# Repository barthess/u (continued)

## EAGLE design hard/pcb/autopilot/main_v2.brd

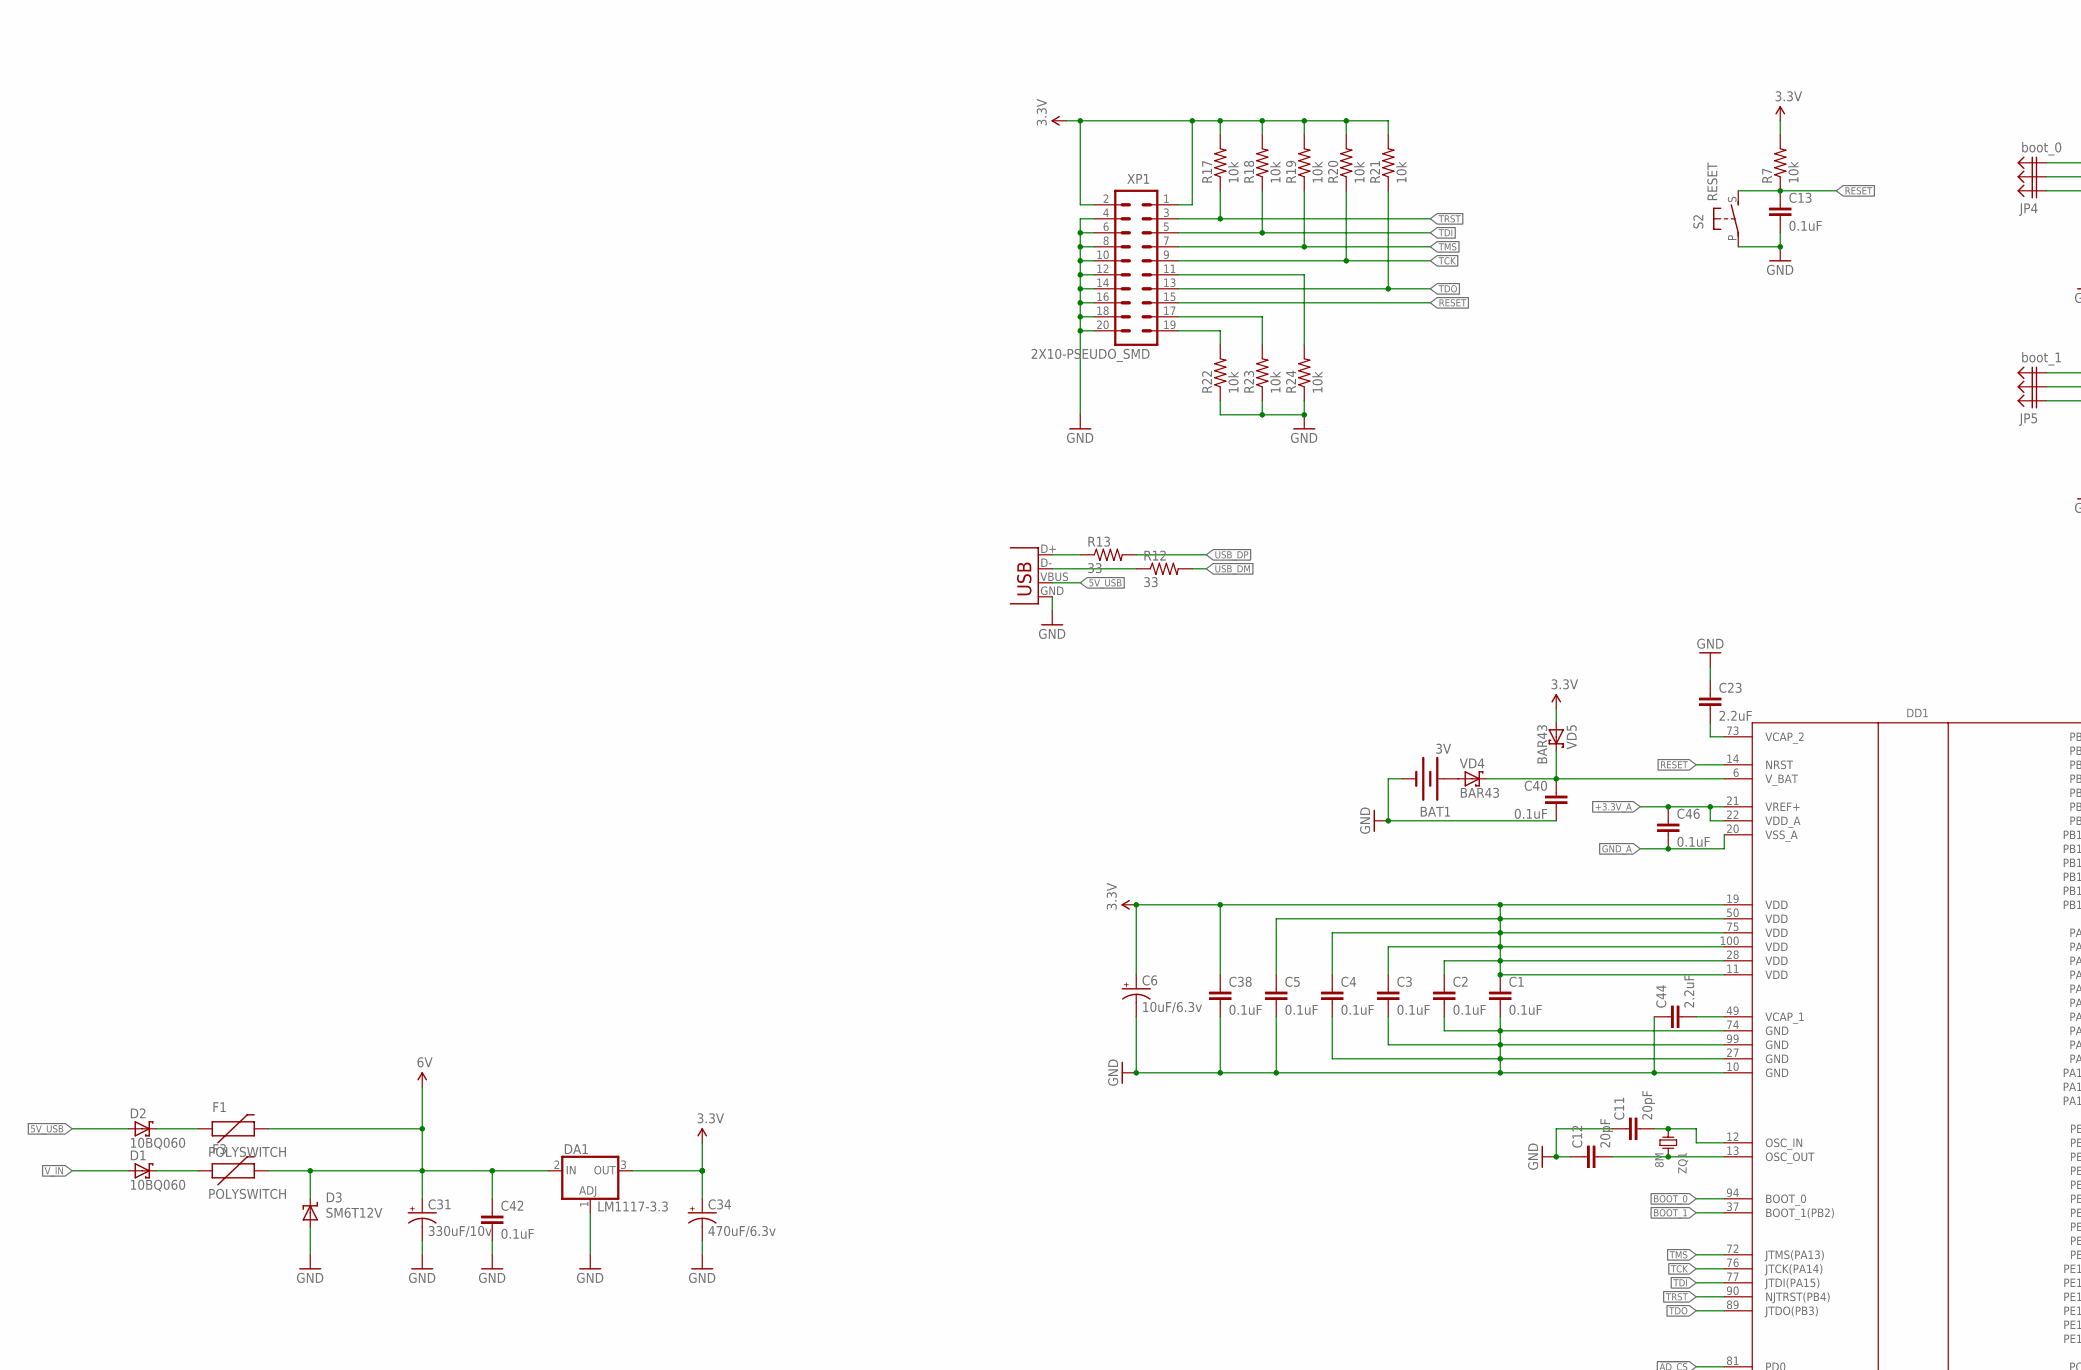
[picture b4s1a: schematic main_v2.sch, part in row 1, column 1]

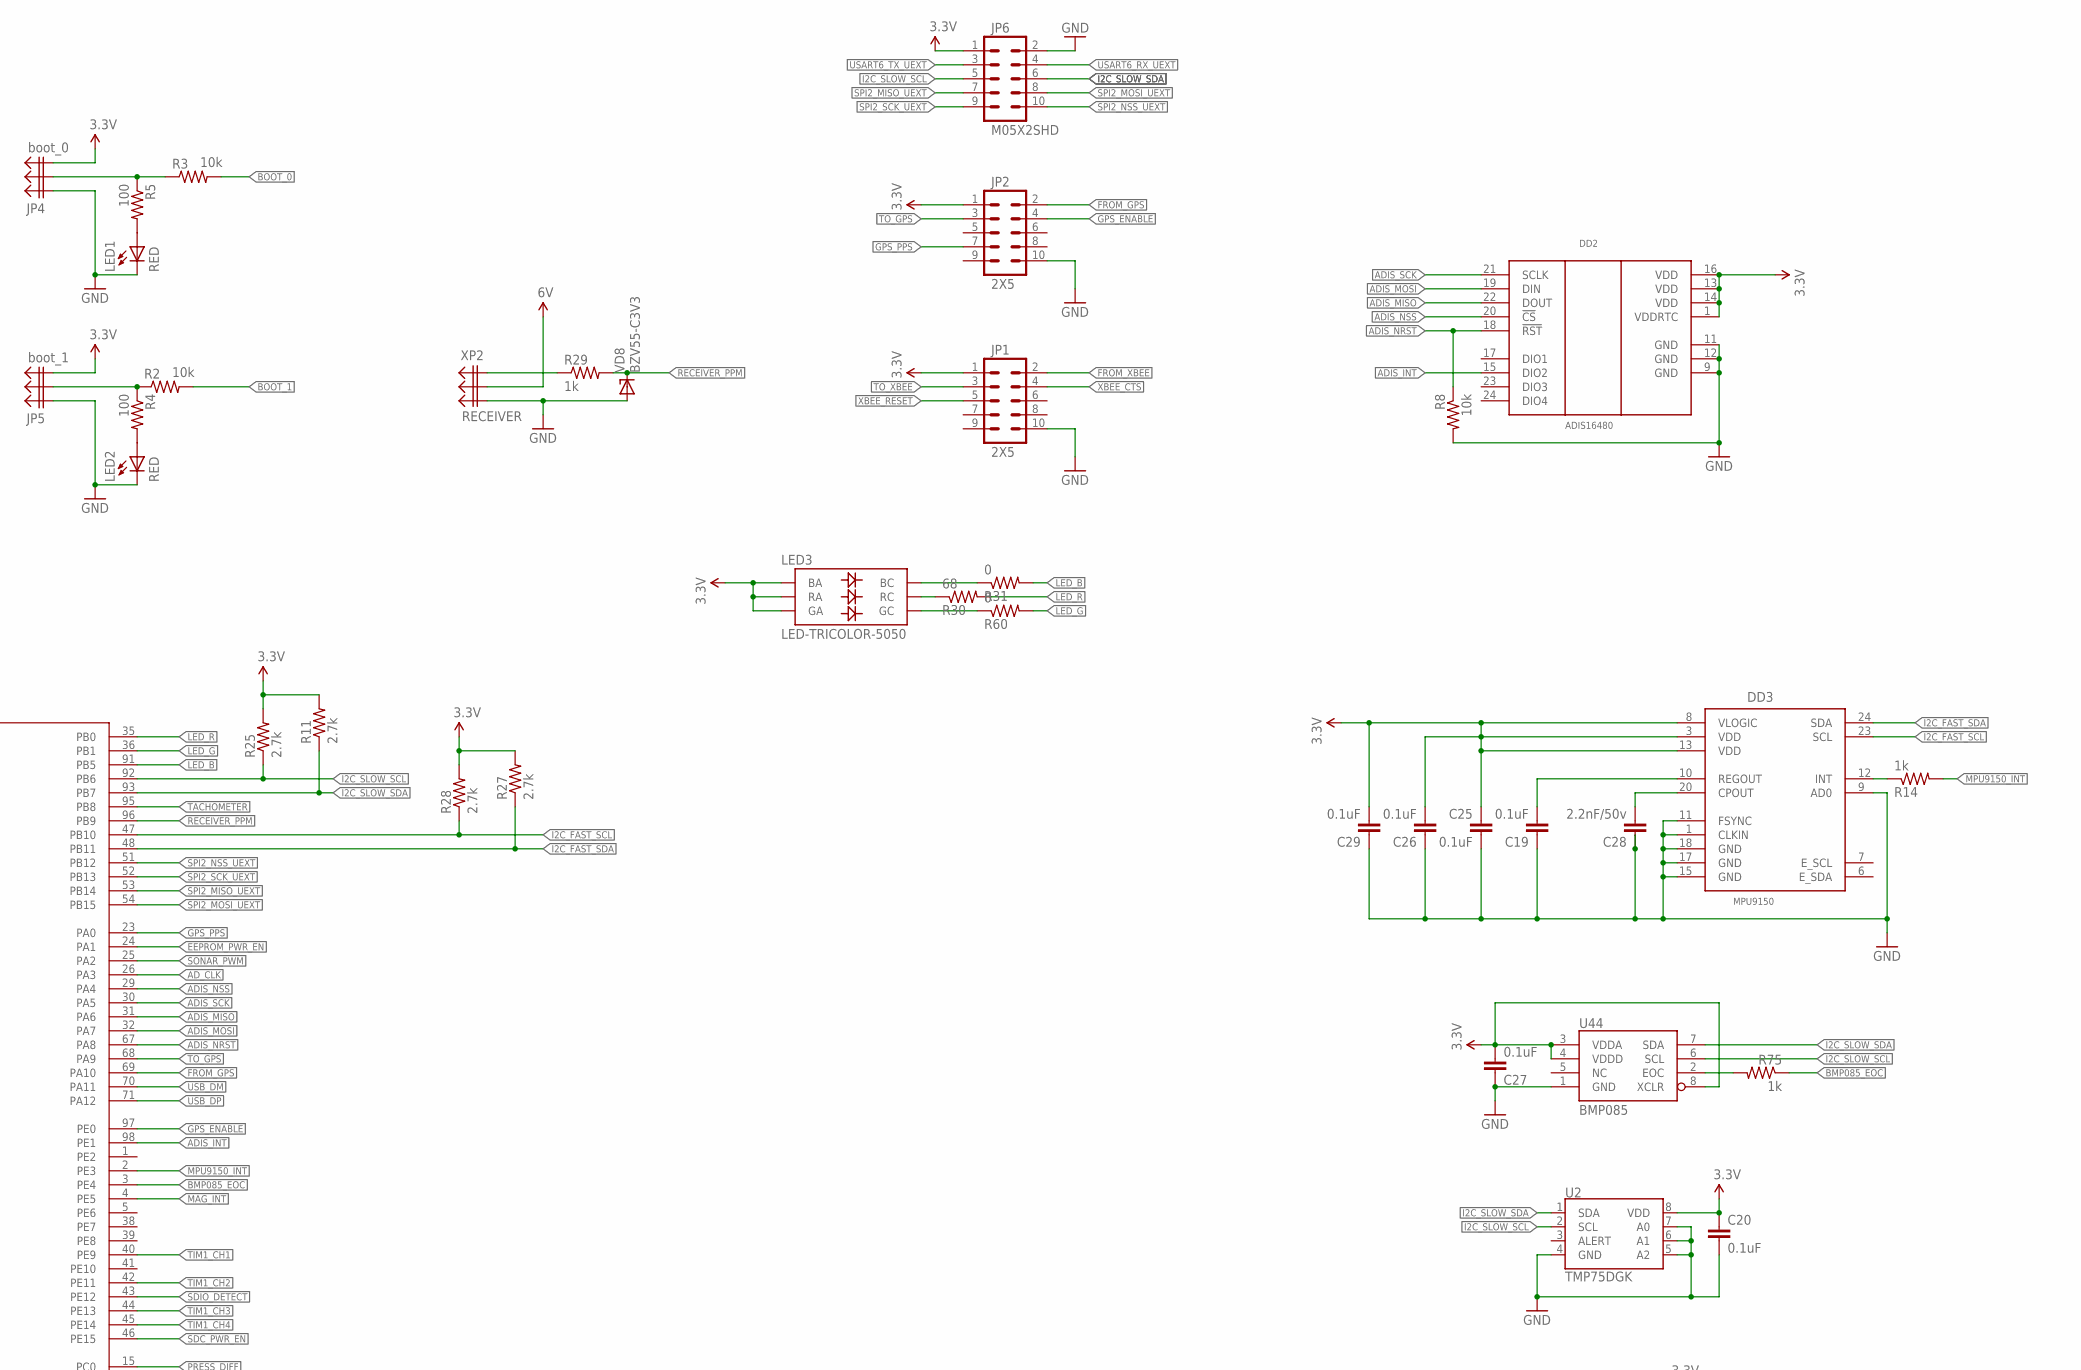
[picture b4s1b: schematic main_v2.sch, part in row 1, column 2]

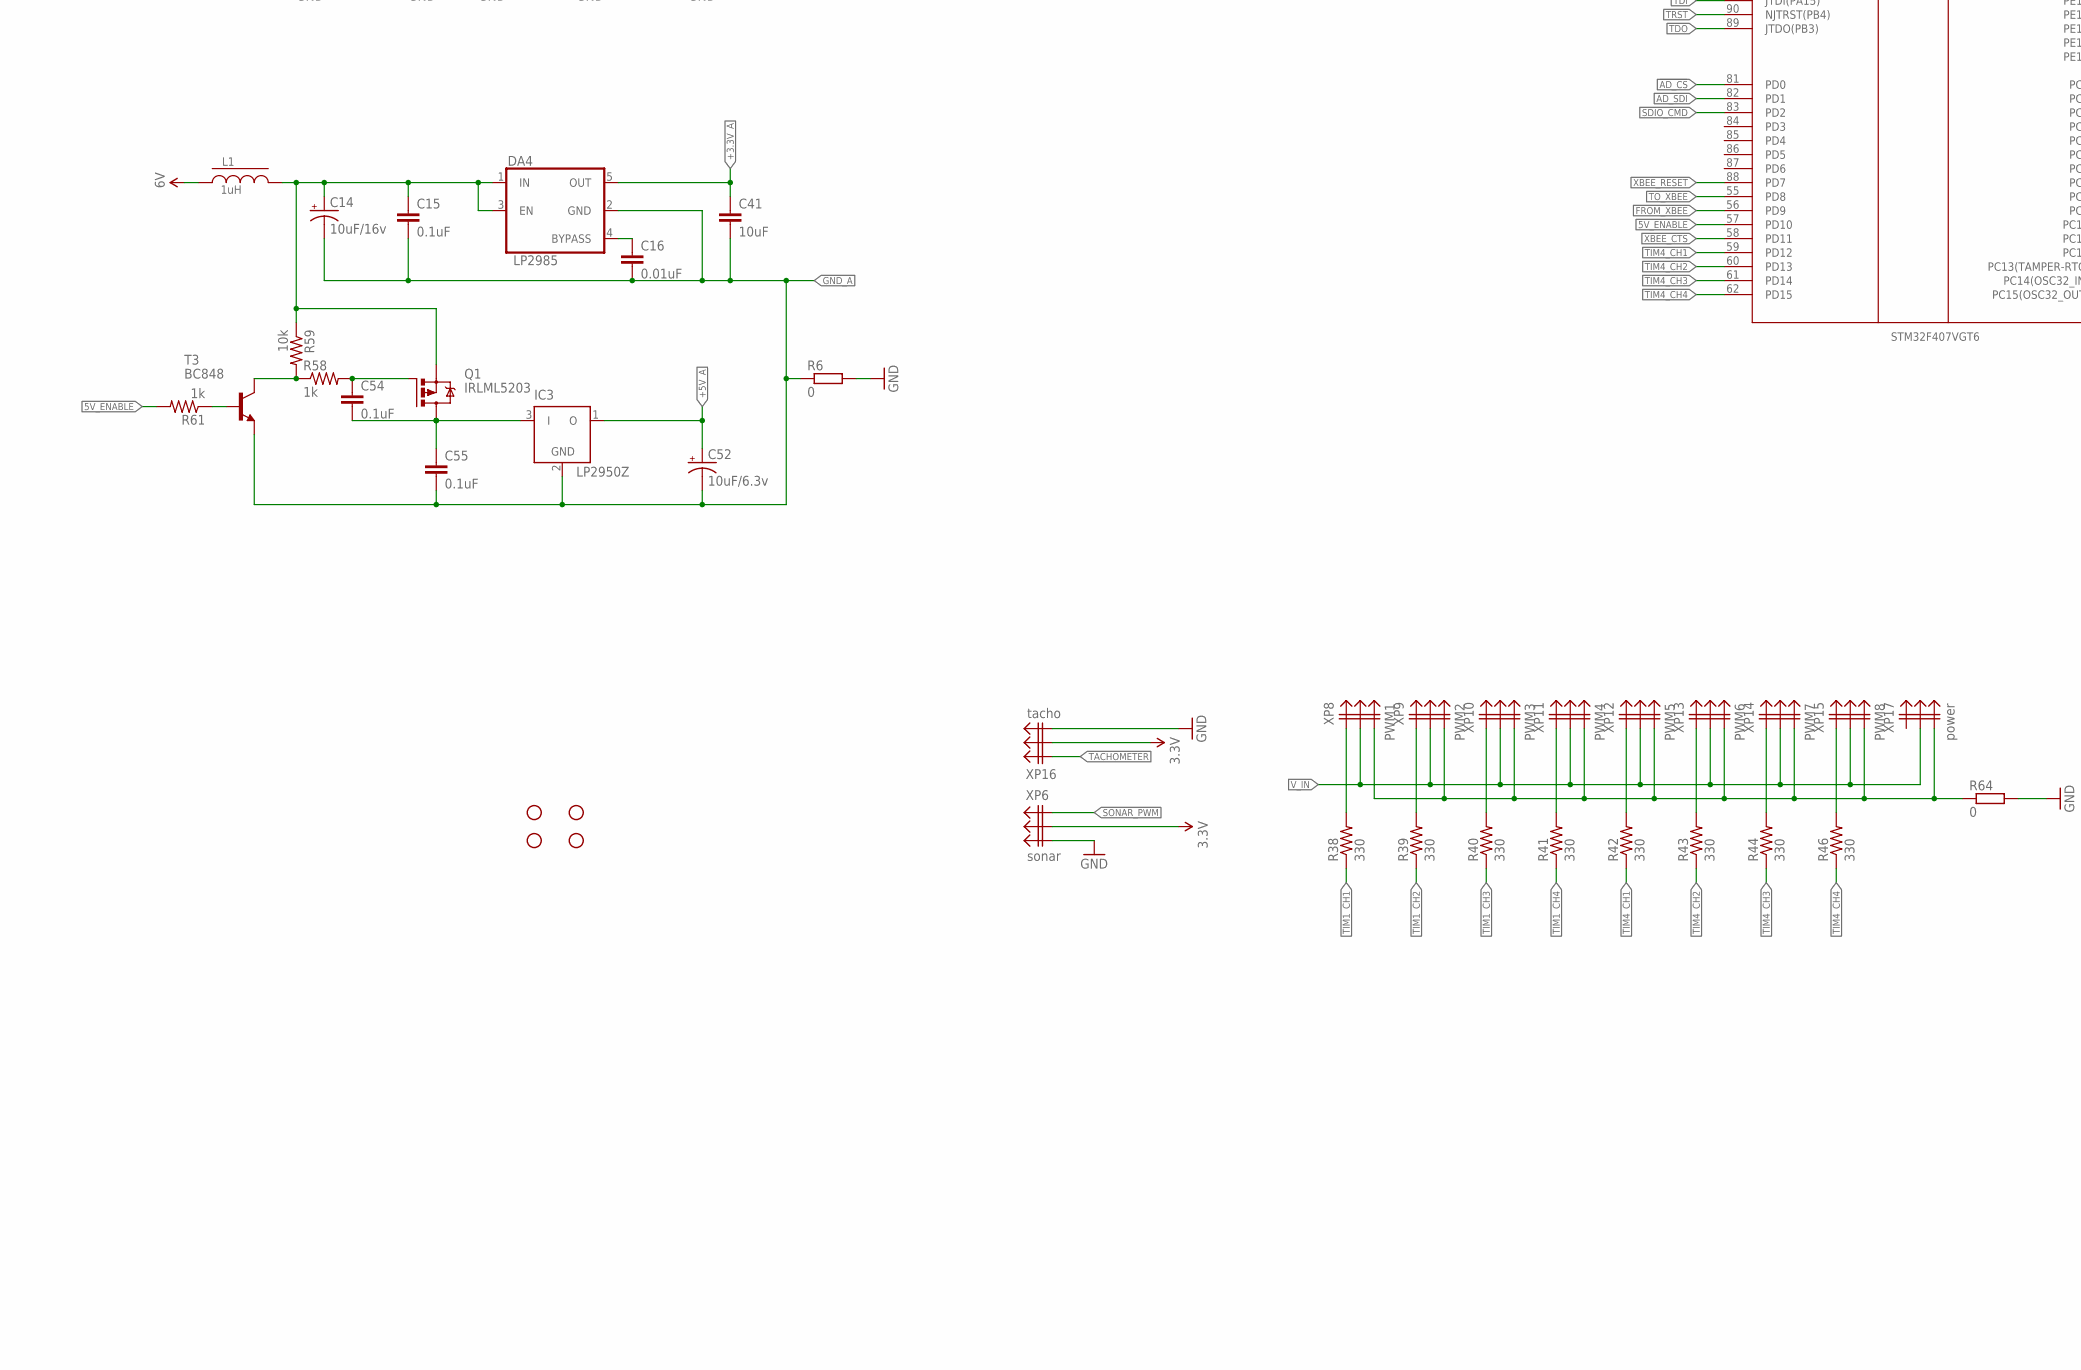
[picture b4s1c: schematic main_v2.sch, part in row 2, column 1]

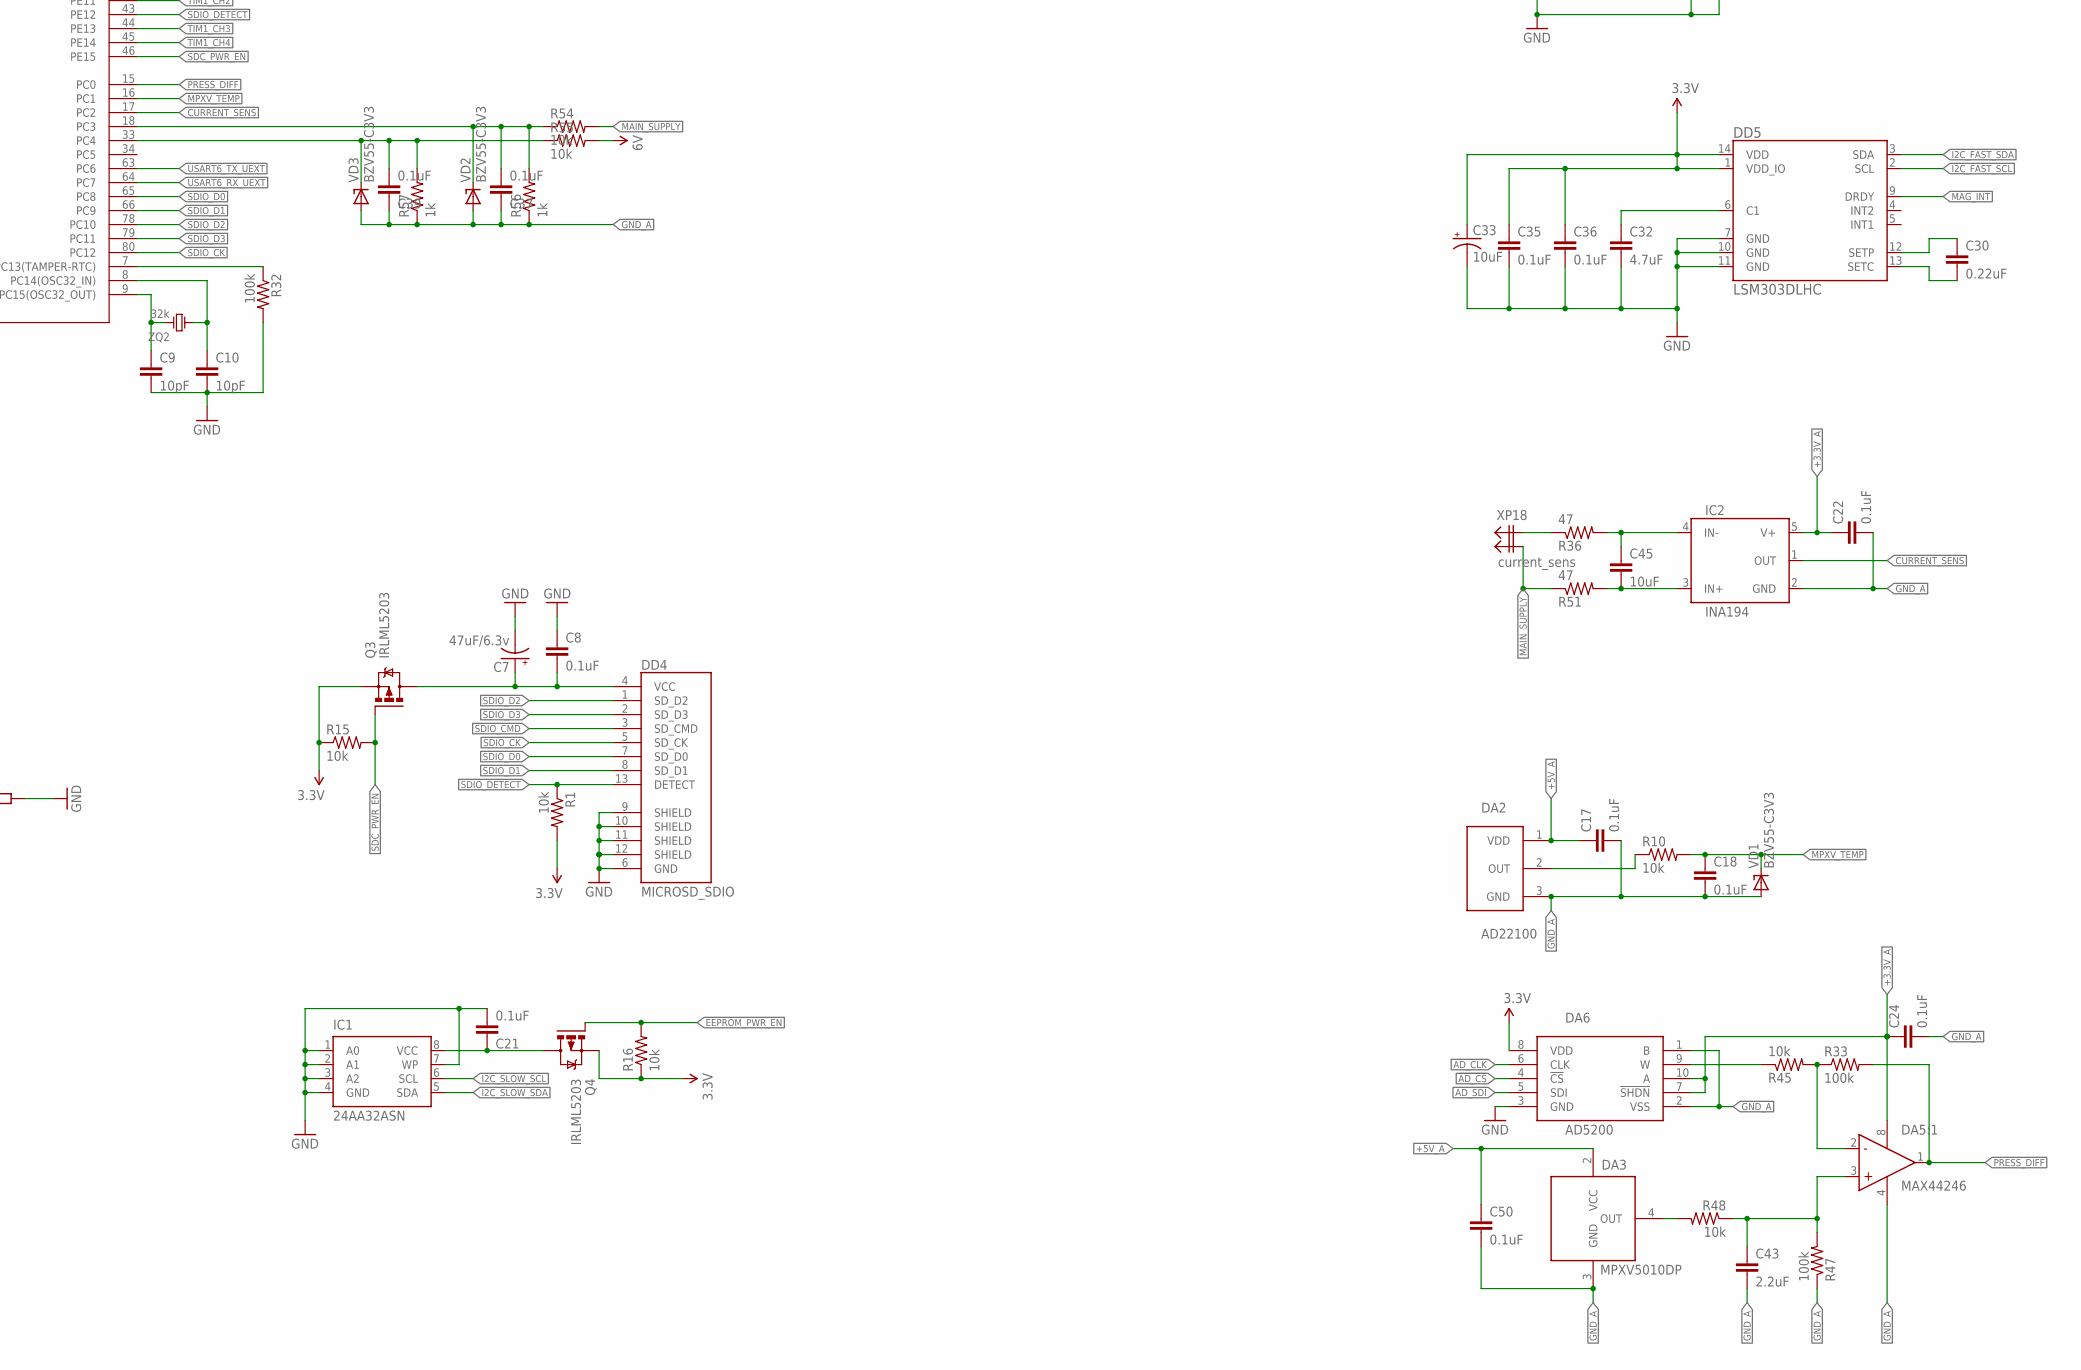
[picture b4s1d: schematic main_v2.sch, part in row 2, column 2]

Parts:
BAT1: 3V; BATTCOM_20MM_PTH
C1, C2, C3, C4, C5, C8, C13, C15, C17, C18, C19, C20, C21, C22, C24, C25, C26, C27, C29, C35, C36, C37, C38, C39, C40, C42, C46, C50, C54, C55: 0.1uF; 0805
C6, C52: 10uF/6.3v; EIA3216-KIT
C7: 47uF/6.3v; EIA3216-KIT
C9, C10: 10pF; 0805
C11, C12: 20pF; 0805
C14: 10uF/16v; EIA3216-KIT
C16: 0.01uF; 0805
C23, C43, C44: 2.2uF; 0805
C28: 2.2nF/50v; 0805
C30: 0.22uF; 0805
C31: 330uF/10v; EIA7343
C32: 4.7uF; 0805
C33: 10uF; EIA3216-KIT
C34: 470uF/6.3v; EIA7343
C41, C45: 10uF; 1206
D1, D2: 10BQ060; SMB
D3: SM6T12V; SMBJ
DA1: LM1117-3.3; TO252
DA2: AD22100; TO92
DA3: MPXV5010DP; 482
DA4: LP2985; SOT23-5
DA5: MAX44246; MSOP8
DA6: AD5200; MSOP10
DD1: STM32F407VGT6; TQFP100
DD2: ADIS16480
DD3: MPU9150; QFN-24-NP
DD4: MICROSD_SDIO; MICROSD
DD5: LSM303DLHC; LGA14
F1, F3: POLYSWITCH; 1812
IC1: 24AA32ASN; SO-08
IC2: INA194; SOT23-5
IC3: LP2950Z; TO92
JP1, JP2: 2X5; PLD_2X05_PSEUDOSMD
JP3, JP7, JP8, JP9: STAND-OFF
JP4: boot_0; PLD_1X03
JP5: boot_1; PLD_1X03
JP6: M05X2SHD; 2X5-SHROUDED
L1: 1uH; L0603
LED1, LED2: RED; LED-0805
LED3: LED-TRICOLOR-5050
Q1, Q3, Q4: IRLML5203; MICRO3
R1, R2, R3, R7, R8, R10, R15, R16, R17, R18, R19, R20, R21, R22, R23, R24, R45, R48, R54, R55, R59: 10k; 0805
R4, R5: 100; 0805
R6, R64: 0; 1206
R11, R25, R27, R28: 2.7k; 0805
R12, R13: 33; 0805
R14, R29, R56, R57, R58, R61, R75: 1k; 0805
R30: 68; 0805
R31, R60: 0; 0805
R32, R33, R47: 100k; 0805
R36, R51: 47; 0805
R38, R39, R40, R41, R42, R43, R44, R46: 330; 0805
S2: RESET; BUTTON_6X3.5
T3: BC848; SOT23
U2: TMP75DGK; MSOP8
U44: BMP085
VD1, VD2, VD3, VD8: BZV55-C3V3; SOD80C
VD4, VD5: BAR43; SOT23-3
X1: USB-SMD-NS; USB-MINIB-NOSTOP
XP1: 2X10-PSEUDO_SMD; PLD_2X10_PSEUDOSMD
XP2: RECEIVER; PLD_1X03
XP6: sonar; PLD_1X03
XP8: PWM1; PLD_1X03
XP9: PWM2; PLD_1X03
XP10: PWM3; PLD_1X03
XP11: PWM4; PLD_1X03
XP12: PWM5; PLD_1X03
XP13: PWM6; PLD_1X03
XP14: PWM7; PLD_1X03
XP15: PWM8; PLD_1X03
XP16: tacho; PLD_1X03
XP17: power; PLD_1X03
XP18: current_sens; PLD_1X02
ZQ1: 8M; CRYSTAL-SMD-5X3
ZQ2: 32k; CRYSTAL-32KHZ-SMD-3.2X1.5

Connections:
3.3V: C1.1, C2.1, C3.1, C4.1, C5.1, C6.A (+), C20.1, C25.1, C26.2, C27.2, C29.2, C33.A (+), C34.A (+), C35.1, C36.1, C38.1, DA1.3 (OUT), DA6.8 (VDD), DD1.11 (VDD), DD1.19 (VDD), DD1.28 (VDD), DD1.50 (VDD), DD1.75 (VDD), DD1.100 (VDD), DD2.1 (VDDRTC), DD2.13 (VDD), DD2.14 (VDD), DD2.16 (VDD), DD3.3 (VDD), DD3.8 (VLOGIC), DD3.13 (VDD), DD5.1 (VDD_IO), DD5.14 (VDD), JP1.1, JP2.1, JP4.3, JP5.3, JP6.1, LED3.1 (BA), LED3.2 (RA), LED3.3 (GA), Q3.2 (S), Q4.2 (S), R1.2, R7.2, R11.2, R15.1, R16.1, R17.2, R18.2, R19.2, R20.2, R21.2, R25.2, R27.2, R28.2, U2.8 (VDD), U44.3 (VDDA), U44.4 (VDDD), U44.8 (XCLR), VD5.1 (A), XP1.1, XP1.2, XP6.2, XP16.2
5V_ENABLE: DD1.57 (PD10), R61.2
5V_USB: D2.A, X1.VBUS
6V: C31.A (+), C42.1, D3.C, DA1.2 (IN), F1.2, F3.2, L1.1, R55.2, XP2.2
!AD_CS: DA6.4 (!CS), DD1.81 (PD0)
+3.3V_A: C22.1, C24.1, C41.1, C46.1, DA4.5 (OUT), DA5.8 (+V), DA6.7 (!SHDN), DA6.10 (A), DD1.21 (VREF+), DD1.22 (VDD_A), IC2.5 (V+)
+5V_A: C17.1, C50.1, C52.A (+), DA2.1 (VDD), DA3.2 (VCC), IC3.1 (O)
ADIS_INT: DD1.98 (PE1), DD2.15 (DIO2)
ADIS_MISO: DD1.31 (PA6), DD2.22 (DOUT)
ADIS_MOSI: DD1.32 (PA7), DD2.19 (DIN)
ADIS_NRST: DD1.67 (PA8), DD2.18 (!RST), R8.1
ADIS_NSS: DD1.29 (PA4), DD2.20 (!CS)
ADIS_SCK: DD1.30 (PA5), DD2.21 (SCLK)
AD_CLK: DA6.6 (CLK), DD1.26 (PA3)
AD_SDI: DA6.5 (SDI), DD1.82 (PD1)
BMP085_EOC: DD1.3 (PE4), R75.1
BOOT_0: DD1.94 (BOOT_0), R3.2
BOOT_1: DD1.37 (BOOT_1(PB2)), R2.2
CURRENT_SENS: DD1.17 (PC2), IC2.1 (OUT)
EEPROM_PWR_EN: DD1.24 (PA1), Q4.1 (G), R16.2
FROM_GPS: DD1.69 (PA10), JP2.2
FROM_XBEE: DD1.56 (PD9), JP1.2
GND: BAT1.2 (-), C1.2, C2.2, C3.2, C4.2, C5.2, C6.C (-), C7.C (-), C8.1, C9.2, C10.2, C11.1, C12.1, C13.2, C19.1, C20.2, C21.2, C23.1, C25.2, C26.1, C27.1, C28.1, C29.1, C31.C (-), C32.2, C33.C (-), C34.C (-), C35.2, C36.2, C38.2, C40.2, C42.2, C44.1, D3.A, DA1.1 (ADJ), DA6.3 (GND), DD1.10 (GND), DD1.27 (GND), DD1.74 (GND), DD1.99 (GND), DD2.9 (GND), DD2.11 (GND), DD2.12 (GND), DD3.1 (CLKIN), DD3.9 (AD0), DD3.11 (FSYNC), DD3.15 (GND), DD3.17 (GND), DD3.18 (GND), DD4.6 (GND), DD4.9 (SHIELD), DD4.10 (SHIELD), DD4.11 (SHIELD), DD4.12 (SHIELD), DD5.7 (GND), DD5.10 (GND), DD5.11 (GND), IC1.1 (A0), IC1.2 (A1), IC1.3 (A2), IC1.4 (GND), IC1.7 (WP), JP1.10, JP2.10, JP4.1, JP5.1, JP6.2, LED1.C, LED2.C, R6.2, R8.2, R22.1, R23.1, R24.1, R32.2, R64.2, S2.P, U2.4 (GND), U2.5 (A2), U2.6 (A1), U2.7 (A0), U44.1 (GND), VD8.A, X1.GND, XP1.4, XP1.6, XP1.8, XP1.10, XP1.12, XP1.14, XP1.16, XP1.18, XP1.20, XP2.3, XP6.3, XP16.3
GND_A: C14.C (-), C15.2, C16.2, C17.2, C18.2, C22.2, C24.2, C37.1, C39.1, C41.2, C43.2, C46.2, C50.2, C52.C (-), C55.2, DA2.3 (GND), DA3.3 (GND), DA4.2 (GND), DA5.4 (-V), DA6.1 (B), DA6.2 (VSS), DD1.20 (VSS_A), IC2.2 (GND), IC3.2 (GND), R6.1, R47.1, R56.1, R57.1, T3.2 (E), VD1.A, VD2.A, VD3.A
GPS_ENABLE: DD1.97 (PE0), JP2.4
GPS_PPS: DD1.23 (PA0), JP2.7
I2C_FAST_SCL: DD1.47 (PB10), DD3.23 (SCL), DD5.2 (SCL), R28.1
I2C_FAST_SDA: DD1.48 (PB11), DD3.24 (SDA), DD5.3 (SDA), R27.1
I2C_SLOW_SCL: DD1.92 (PB6), IC1.6 (SCL), JP6.5, R25.1, U2.2 (SCL), U44.6 (SCL)
I2C_SLOW_SDA: DD1.93 (PB7), IC1.5 (SDA), JP6.6, R11.1, U2.1 (SDA), U44.7 (SDA)
LED_B: DD1.91 (PB5), R31.2
LED_G: DD1.36 (PB1), R60.2
LED_R: DD1.35 (PB0), R30.2
MAG_INT: DD1.4 (PE5), DD5.9 (DRDY)
MAIN_SUPPLY: R51.1, R54.2, XP18.2
MPU9150_INT: DD1.2 (PE3), R14.2
MPXV_TEMP: C18.1, DD1.16 (PC1), R10.2, VD1.C
unnamed: C9.1, DD1.9 (PC15(OSC32_OUT)), ZQ2.2
unnamed: LED2.A, R4.2
unnamed: JP5.2, R2.1, R4.1
unnamed: LED1.A, R5.2
unnamed: JP4.2, R3.1, R5.1
unnamed: C10.1, DD1.8 (PC14(OSC32_IN)), ZQ2.1
unnamed: C12.2, DD1.13 (OSC_OUT), ZQ1.3
unnamed: LED3.6 (BC), R31.1
unnamed: C11.2, DD1.12 (OSC_IN), ZQ1.1
unnamed: R12.1, X1.D-
unnamed: DA6.9 (W), R45.1
unnamed: LED3.5 (RC), R30.1
unnamed: R13.1, X1.D+
unnamed: D1.C, F3.1
unnamed: C16.1, DA4.4 (BYPASS)
unnamed: DA2.2 (OUT), R10.1
unnamed: R22.2, XP1.19
unnamed: R23.2, XP1.17
unnamed: R24.2, XP1.11
unnamed: C45.1, IC2.4 (IN-), R36.2
unnamed: C28.2, DD3.20 (CPOUT)
unnamed: C19.2, DD3.10 (REGOUT)
unnamed: C7.A (+), C8.2, DD4.4 (VCC), Q3.3 (D)
unnamed: C30.1, DD5.12 (SETP)
unnamed: C21.1, IC1.8 (VCC), Q4.3 (D)
unnamed: DD3.12 (INT), R14.1
unnamed: C30.2, DD5.13 (SETC)
unnamed: C32.1, DD5.6 (C1)
unnamed: BAT1.1 (+), VD4.1 (A)
unnamed: C14.A (+), C15.1, DA4.1 (IN), DA4.3 (EN), L1.2, Q1.2 (S), R59.1
unnamed: LED3.4 (GC), R60.1
unnamed: R29.1, XP2.1
unnamed: C40.1, DD1.6 (V_BAT), VD4.3 (C), VD5.3 (C)
unnamed: DD1.7 (PC13(TAMPER-RTC)), R32.1
unnamed: DA3.4 (OUT), R48.2
unnamed: D2.C, F1.1
unnamed: C45.2, IC2.3 (IN+), R51.2
unnamed: R36.1, XP18.1
unnamed: DA5.2 (-IN), R33.1, R45.2
unnamed: C43.1, DA5.3 (+IN), R47.2, R48.1
unnamed: C37.2, DD1.18 (PC3), R54.1, R56.2, VD2.C
unnamed: C54.1, Q1.1 (G), R58.2
unnamed: C39.2, DD1.33 (PC4), R55.1, R57.2, VD3.C
unnamed: C54.2, C55.1, IC3.3 (I), Q1.3 (D)
unnamed: R61.1, T3.1 (B)
unnamed: R75.2, U44.2 (EOC)
unnamed: R64.1, XP8.3, XP9.3, XP10.3, XP11.3, XP12.3, XP13.3, XP14.3, XP15.3, XP17.3
unnamed: C23.2, DD1.73 (VCAP_2)
unnamed: C44.2, DD1.49 (VCAP_1)
NET$1: R58.1, R59.2, T3.3 (C)
PRESS_DIFF: DA5.1 (OUT), DD1.15 (PC0), R33.2
PWM1: R38.2, XP8.1
PWM2: R39.2, XP9.1
PWM3: R40.2, XP10.1
PWM4: R41.2, XP11.1
PWM5: R42.2, XP12.1
PWM6: R43.2, XP13.1
PWM7: R44.2, XP14.1
PWM8: R46.2, XP15.1
RECEIVER_PPM: DD1.96 (PB9), R29.2, VD8.C
RESET: C13.1, DD1.14 (NRST), R7.1, S2.S, XP1.15
SDC_PWR_EN: DD1.46 (PE15), Q3.1 (G), R15.2
SDIO_CK: DD1.80 (PC12), DD4.5 (SD_CK)
SDIO_CMD: DD1.83 (PD2), DD4.3 (SD_CMD)
SDIO_D0: DD1.65 (PC8), DD4.7 (SD_D0)
SDIO_D1: DD1.66 (PC9), DD4.8 (SD_D1)
SDIO_D2: DD1.78 (PC10), DD4.1 (SD_D2)
SDIO_D3: DD1.79 (PC11), DD4.2 (SD_D3)
SDIO_DETECT: DD1.43 (PE12), DD4.13 (DETECT), R1.1
SONAR_PWM: DD1.25 (PA2), XP6.1
SPI2_MISO_UEXT: DD1.53 (PB14), JP6.7
SPI2_MOSI_UEXT: DD1.54 (PB15), JP6.8
SPI2_NSS_UEXT: DD1.51 (PB12), JP6.10
SPI2_SCK_UEXT: DD1.52 (PB13), JP6.9
TACHOMETER: DD1.95 (PB8), XP16.1
TCK: DD1.76 (JTCK(PA14)), R20.1, XP1.9
TDI: DD1.77 (JTDI(PA15)), R18.1, XP1.5
TDO: DD1.89 (JTDO(PB3)), R21.1, XP1.13
TIM1_CH1: DD1.40 (PE9), R38.1
TIM1_CH2: DD1.42 (PE11), R39.1
TIM1_CH3: DD1.44 (PE13), R40.1
TIM1_CH4: DD1.45 (PE14), R41.1
TIM4_CH1: DD1.59 (PD12), R42.1
TIM4_CH2: DD1.60 (PD13), R43.1
TIM4_CH3: DD1.61 (PD14), R44.1
TIM4_CH4: DD1.62 (PD15), R46.1
TMS: DD1.72 (JTMS(PA13)), R19.1, XP1.7
TO_GPS: DD1.68 (PA9), JP2.3
TO_XBEE: DD1.55 (PD8), JP1.3
TRST: DD1.90 (NJTRST(PB4)), R17.1, XP1.3
USART6_RX_UEXT: DD1.64 (PC7), JP6.4
USART6_TX_UEXT: DD1.63 (PC6), JP6.3
USB_DM: DD1.70 (PA11), R12.2
USB_DP: DD1.71 (PA12), R13.2
V_IN: D1.A, XP8.2, XP9.2, XP10.2, XP11.2, XP12.2, XP13.2, XP14.2, XP15.2, XP17.2
XBEE_CTS: DD1.58 (PD11), JP1.4
XBEE_RESET: DD1.88 (PD7), JP1.5

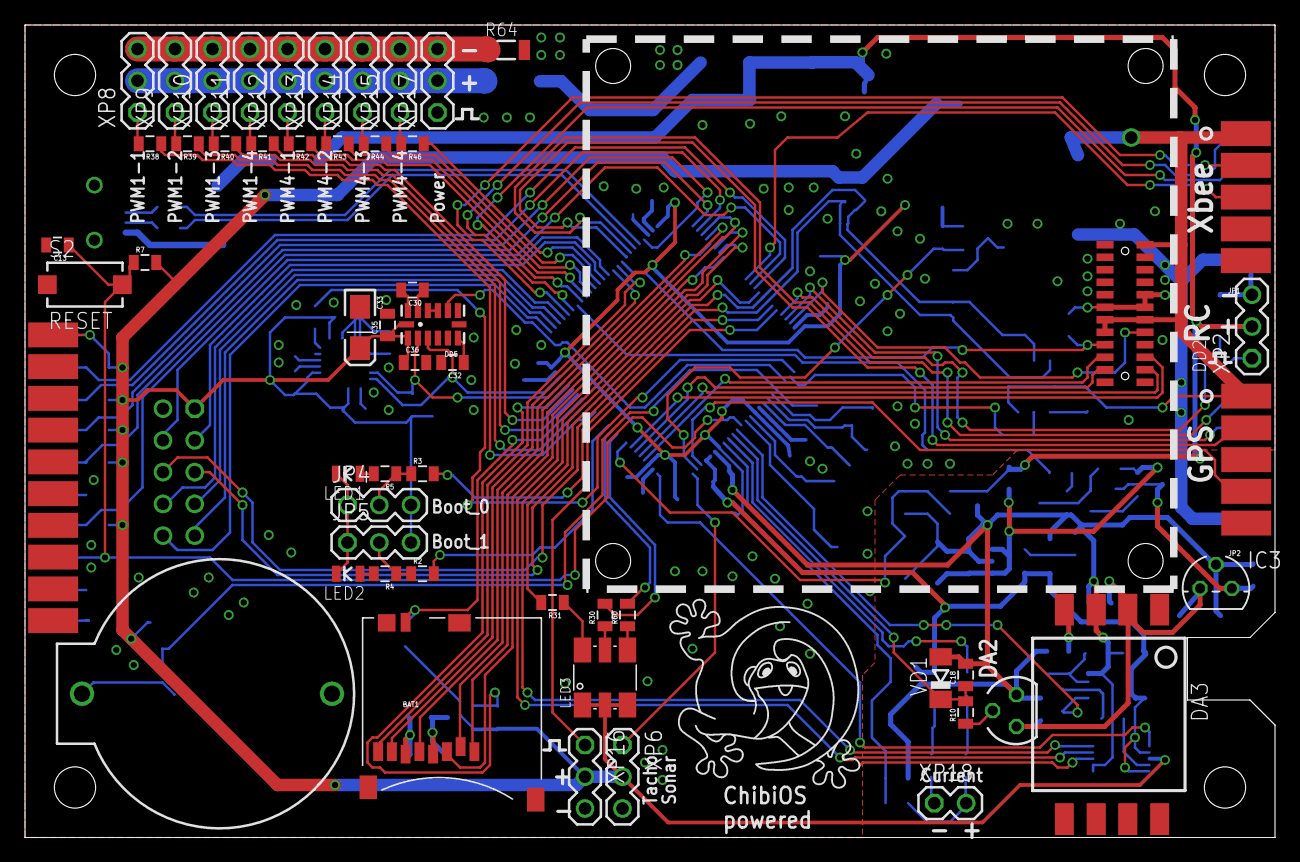
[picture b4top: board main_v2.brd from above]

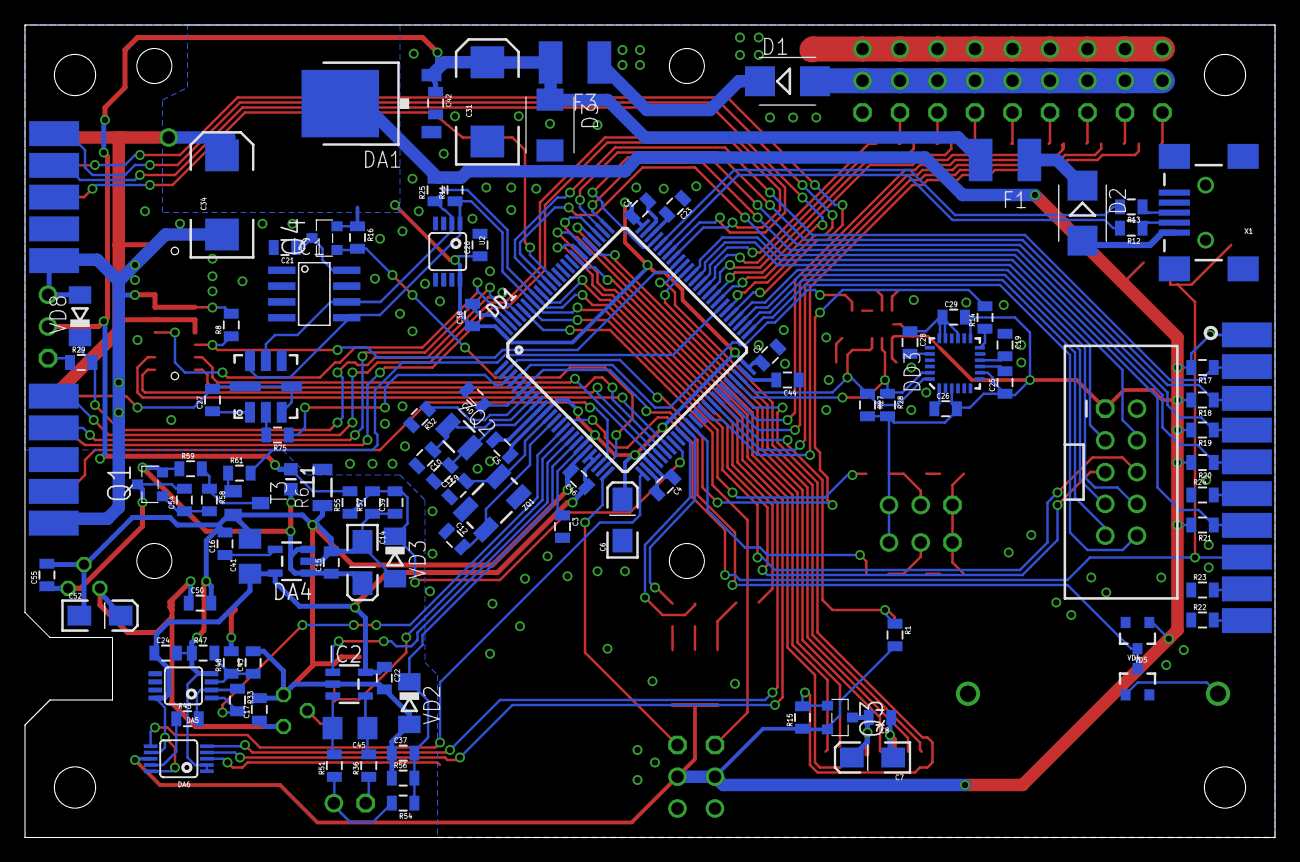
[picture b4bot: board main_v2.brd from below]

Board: 2 copper layers, 100.0 x 65.0 mm, 168 parts (109 on the bottom side), 134 nets.

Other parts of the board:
U$2: LOGO_CHIBIOS_SILK

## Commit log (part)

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2012-09-21 updated todo
2012-09-22 adc waiting code switched off
2012-09-22 sqrtf() based code of deciding if reaching waypoint\
2012-09-22 added max and min speed limits
2012-09-22 updated todo"
    test string
2012-09-22 added wfi switch
2012-09-22 logger improvements
2012-09-22 cosmetic improvements
2012-09-22 added time handling CLI
2012-09-22 parameter CLI improvement
2012-09-22 timezone handling optimization
2012-09-23 rewritten log scheduler helper
2012-09-23 added sending ability of mavlink_nav_controller_output and mavlink_local_position_ned
2012-09-24 renamed stubs to gcc_stubs
2012-09-24 gps data writes in log now even if now valid coordinates
2012-09-24 cosmetical improvements
2012-09-24 deleted unused files
2012-09-24 cleanups
2012-09-24 added dbugging messaging ability
2012-09-24 minor pid refactoring
2012-09-24 added climb rate calculation
2012-09-24 magnetic declination must be substructed (not added) to yaw
2012-09-24 renamed dir
2012-09-24 added style sheets with tahoma font
2012-09-24 added alpha-beta filter for heading. Not tested at all
2012-09-25 in course alpha-beta function added angle wrapping
2012-09-25 commented out unusable alpha-beta filtering for course
2012-09-25 fixing setting of date from gps
2012-09-25 added todo
2012-09-26 file renames
2012-09-26 file structure reorganization
2012-09-26 stab.c splitted to smaller files
2012-09-26 ground rover liter code moved
2012-09-26 added climb meter in bmp085 code
2012-09-27 some files renamed
2012-10-02 bmp085 code refactoring
2012-10-04 added CLI applet to show DCM
2012-10-04 file renaming
2012-10-05 global flags rewritted to bit fields
2012-10-05 deleted unused global flags
2012-10-09 fixed potential bug with pointer to dynamically created thread
2012-10-09 fixed potential overflow in GPS
2012-10-09 fixed minor bug in GPS
2012-10-10 switched on FPU
2012-10-11 fixed date setting interface
2012-10-11 cosmetic CLI improvement
2012-10-11 calculated some files with constants for different SYS_CLK values
2012-10-11 PLL external settings improvements
2012-10-12 fault handlers cosmetic improvements
2012-10-12 current sensing improvements
2012-10-12 fix for previouse commit
2012-10-12 new TODO
2012-10-12 added PLL_24MHz.h
2012-10-12 slightly increased timout to avoid tiring
2012-10-12 cosmetic improvements in CLI
2012-10-14 improved hardfault handler
2012-10-14 code cleanups
2012-10-14 static optimizations
2012-10-14 cli code cleanups
2012-10-14 some static optimizations
2012-10-15 stable catching of bug
2012-10-16 changes storage qualifier to const for airspeed table
2012-10-17 returning pointers to dynamically created threads moved to static variables
2012-10-21 readability improvement
2012-10-21 deleted old code
2012-10-21 added 64MHz setting file for PLL
2012-10-23 changes caused by new eeprom driver
2012-10-24 all shell commands now receive pointer to serial driver as parameter
2012-10-27 RAM consumption optimizations
2012-10-27 softrest on panic done. Need to modifie boot process to gain boot speed bonuses
2012-10-27 add some checks to prevent initialization before parameters acquired from eeprom
2012-10-27 prev. commit improvements
2012-10-28 i2c sensors' init code split to full and short parts
2012-10-28 fixed fast boot logic
2012-10-28 added whoami checking in itg3200 startup code
2012-10-28 fixed whoami testing for ITG3200
2012-10-28 removed small sleeps in i2c startup blocks
2012-10-28 added hardcoded value for gyro update period
2012-10-28 increased stack size for i2c sensors threads
2012-10-28 added ability to save single param value to eeprom
2012-10-29 now panic handler automatically break if runs under debugger
2012-10-29 added eeprom config header
2012-10-29 do some rewriting of gyro calibration
2012-10-29 fixed wrong axis placement
2012-10-30 improved uav specific widget for QGC
2012-10-30 soft reset handles correctly for now
2012-10-30 file rename
2012-11-02 todo updates
2012-11-03 parameter structure now autogenerated
2012-11-03 SEND_OFF value changed from 19 to 0. Telemetry sender changed to correctly handle this situation
2012-11-03 todo changed
2012-11-03 rotation code checked and work
2012-11-03 more candy blue blinker
2012-11-03 autogeneration improvements
2012-11-04 added rules for autogenerated code
2012-11-04 gyro sums removed from global structure
2012-11-04 accelerometer data removed from raw structure
2012-11-04 magnetometer calibration done but not tested
2012-11-04 small refactoring
2012-11-04 calibrating wok
2012-11-04 todo updated
2012-11-05 fixed integer power functions
2012-11-07 rewritten generator for bmp085 table function
2012-11-07 deleted unneded include
2012-11-09 rewrite generator for sorting in function
2012-11-09 sort out totally autogenerated now
2012-11-09 minor convenient fix
2012-11-09 status message turned to static scope
2012-11-22 rewritten resource usage script
2013-01-21 ignore file updated
2013-01-22 packer generation works
2013-01-22 unpacker code compiles
2013-01-22 telemtry sender code generating works
2013-01-23 added detection of OS in Makefile for proper use of ccache
2013-01-23 added old message.c file as cheatsheet
2013-01-23 generation of logger packer function works
2013-01-23 data sending via events works. WPS need to be reworked
2013-01-24 reading waypoints from eeprom works
2013-01-24 saving WPs works
2013-01-24 sending telemetry from virtual timers works
2013-01-24 packer and unpacker now warn about unhanlded messages IDs. Suitable for debug
2013-01-25 separation done
2013-03-01 fixed mistype in comments
2013-03-02 added benchmark template
2013-03-02 added benchmark template step 2
2013-03-02 added USB_CDC support
2013-03-02 cpu loading now calculates more elegant
2013-03-02 cpu loading calculation code moved to timekkeper module
2013-03-17 improved gyro zeroing procedure
2013-03-20 gyro calibration state grouped to single context structure
2013-03-27 added imporved vector and matrix instructions
2013-04-12 added snippet code for LSM303
2013-04-14 tested LSM303 code
2013-04-15 LSM303 fully integrated and tested
2013-04-18 in magnetometer added hardcoded calibration coefficients
2013-04-18 fixed all implicit conversion from float to double
2013-04-18 first successfull build
2013-04-18 i2c starting code compiles
2013-04-18 updated eeprom repo
2013-04-18 eeprom registry builds successfully
2013-04-18 deleted dead code
2013-04-19 updated main chibios path
2013-04-19 tmp75 sensor wrapped to class
2013-04-19 added virtual initialization functions
2013-04-19 mma8451 updated
2013-04-19 bmp085 updated
2013-04-19 asdf
2013-04-19 minor fixes in eeprom code
2013-04-19 compiles almost full source
2013-04-20 first code in wp database
2013-04-20 all compiles successfully now
2013-04-20 deleted old unnede eeprom config
2013-04-20 realized mutual acces to ParamRegistry
2013-04-20 added template class for alphabeta filter
2013-04-21 deleted unneded file
2013-04-21 parameter subsystem updated
2013-04-21 added filter in magnetometer code
2013-04-21 added check for file overflow in param registry
2013-04-22 vector and matrix functions rewritten in template style
2013-04-22 added inverse matrix calculator
2013-04-22 added inplace sorting function
2013-04-23 added cosher parameters backup
2013-04-23 Inverse matrix calculation
    Overloaded fabs() fucntions changed to (T)fabs() to improve
    perfomance. Calculation of 9x9 matrix takes about 125000 ticks.
2013-04-23 added some benchmarks
2013-04-23 removed artificial panic
2013-04-23 Flag denoting fresh mag data removed as deprecated
2013-04-23 Added immobility detector based on accelerometer
    Need to add tunable threshold
2013-04-23 enabled hard FPU
2013-04-24 added matrix multiplication function uses matrix of pointers
2013-04-24 compensated data values convert in arrays
2013-04-25 added immobility detector based on accelerometer
2013-04-25 added immobility detector based on magnetometer
2013-04-25 cleanup
2013-04-25 gyro zeroing works fine
2013-04-25 added madgwick algorithm
2013-04-26 added draft of quaternion math
2013-04-26 AHRS improvements
2013-04-26 added matrix lib sources
2013-04-27 code looks working
2013-04-28 added separate blinker code
2013-04-29 blinkers work fine
2013-04-29 added switcher between intergrated gyroscope angles and angular rates
2013-04-29 minor improvements
2013-04-29 uav.h renamed to main.h
2013-04-29 DSP code cleanups
2013-04-29 matrix library finalized
2013-04-29 quaternion code improvements
2013-04-29 matrix code improvements
2013-04-30 matrix code fixes
2013-04-30 Lots of improvements in AHRS code.
    1) All raw data from sensors now converts to NUE coordinates.
    2) When passed to DCM orientation algorithm they converts
    to NWU
    3) Cleaups in Madgwick algorithm
2013-04-30 madgwick code cleaup
2013-04-30 added switche between mdgwick ahrs and dcm ahrs
2013-04-30 added intrinsic square root function
2013-05-01 cleanups in gyro calibration code
2013-05-01 itg3200 calibrator moved to separate class
2013-05-01 i2c device class refactor
2013-05-01 magnetic values no in uT
2013-05-01 4 point calibration for LSM303 works
2013-05-02 waypoint loading code works
2013-05-02 make subsystem improvements
2013-05-03 class header for pid controller
2013-05-03 added drafe acs_interface
2013-05-03 deleted acs interface example
2013-05-04 added draft ACS
2013-05-04 imu code converted to class
2013-05-05 servo directory renamed to drivetrain
2013-05-05 improved mission planner
2013-05-06 heading and thrust PIDs work
2013-05-06 lots of code cleanups
2013-05-06 deleted unused static i2c sensors
2013-05-07 acs can navigate now
2013-05-07 fixed course estimation
2013-05-08 added great cyrcle navigation code
2013-05-08 minor refactoring
2013-05-09 added test waypoint list
2013-05-11 loitering and pausing done
2013-05-11 loitering code split to subfunctions
2013-05-11 acs file split to parts
2013-05-12 improvements in navigation code
2013-05-12 crosstrack error code tested in software
2013-05-15 ACS improvements
2013-05-15 added stm32-hardfault-backtrace recipe
2013-05-16 ACS now abstract class
2013-05-16 added reset of XTD pid on WP reaching
2013-05-16 cosmetical improvements in pid code
2013-05-16 added some additional warning setting in makefile
2013-05-22 updated eeprom module
2013-05-24 eeprom module updated
2013-05-27 mistype in comment fixed
2013-05-27 chibiutils struct renamed to cliutils
2014-03-31 Board. NOP
2014-04-01 Main board v2 looks finalized
2014-04-01 Added board v2
2014-04-01 Changed in PCB
2014-04-03 Board v2
2014-04-05 board v2 nop
2014-04-06 board v2. nop
2014-04-07 board v2. Minor fixes
2014-04-07 board v2. Added capacitor for ADC
2014-05-19 Added 5mm 3color led
2014-05-26 Added new job file
2014-06-02 Main board. Final cut
2014-06-09 Added definitions for metric gerber
2014-06-09 Fixed job. Deleted outline from top layer
2014-08-18 File cleanup
2014-11-10 Added kalman hardware
2014-11-11 PCB routed
2014-11-11 Board minor fixes
2015-01-26 updated kalman tester
2015-01-26 updated eagle project file
2015-02-08 Updated schematic
2015-02-18 Fixed pinout for external connector
2015-06-02 Added board for GPS receiver
2015-06-03 update gps NEO board
2015-06-26 Added motor driver board
2015-07-04 L239 rework
